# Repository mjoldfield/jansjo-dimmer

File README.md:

# Jansjö dimmer

This repository relates to a simple PWM dimmer designed ostensibly for
the Ikea Jansjö LED lamp.

See [the full article](http://mjoldfield.com/atelier/2017/11/jansjo-dimmer.html)
for more details.

## data

Experimental data from the prototypes:

### dutycycle-f

The variation of frequency with duty-cycle.

    $ gnuplot plotit.scr
    $ open out.pdf

### current-t

Various screen captures from the scope showing current against time.

## datasheets

Manufacturers' data for parts in the project.

## gerbers

PCB files as sent to the board manufacturer (Elecrow).

## kicad

PCB/schematic files

## panel

A Haskell program to generate a PDF to laser cut the front panel.

Given [stack](https://docs.haskellstack.org/en/stable/README/):

    $ stack build
    $ stack exec pdf-exe
    $ open *.pdf

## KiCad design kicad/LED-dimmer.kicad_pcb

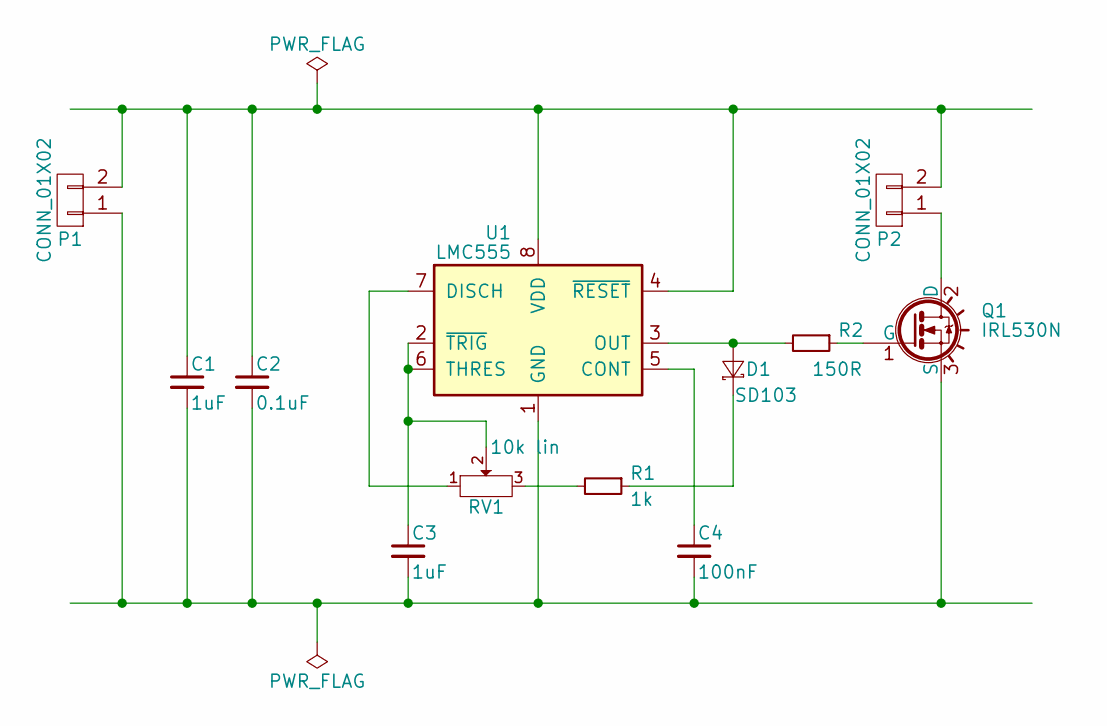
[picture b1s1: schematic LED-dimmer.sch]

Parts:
C1, C3: 1uF; C_0603
C2: 0.1uF; C_0603
C4: 100nF; C_0603
D1: SD103; D_SOD-123
P1, P2: CONN_01X02; Molex_MicroLatch-53253-0270_02x2.00mm_Straight
Q1: IRL530N; TO-263-2
R1: 1k; R_0603
R2: 150R; R_0603
RV1: 10k lin; Potentiometer_WirePads
U1: LMC555; SOIC-8_3.9x4.9mm_Pitch1.27mm

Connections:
unnamed: C1.1, C2.1, P1.2, P2.2, U1.4 (~RESET), U1.8 (VDD)
unnamed: C1.2, C2.2, C3.2, C4.2, P1.1, Q1.3 (S), U1.1 (GND)
unnamed: C3.1, RV1.2, U1.2 (~TRIG), U1.6 (THRES)
unnamed: C4.1, U1.5 (CONT)
unnamed: D1.1 (K), R1.1
unnamed: D1.2 (A), R2.2, U1.3 (OUT)
unnamed: P2.1, Q1.2 (D)
unnamed: Q1.1 (G), R2.1
unnamed: R1.2, RV1.3
unnamed: RV1.1, U1.7 (DISCH)

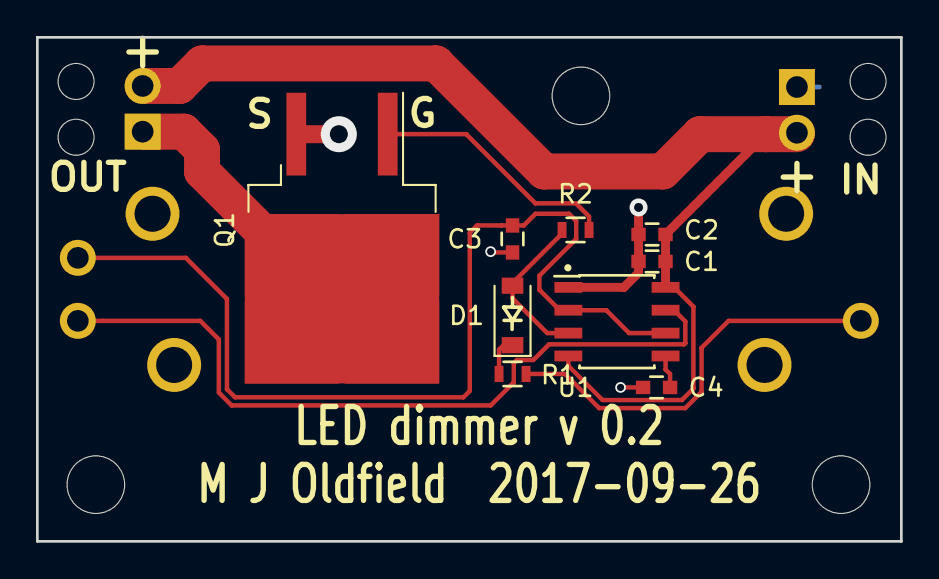
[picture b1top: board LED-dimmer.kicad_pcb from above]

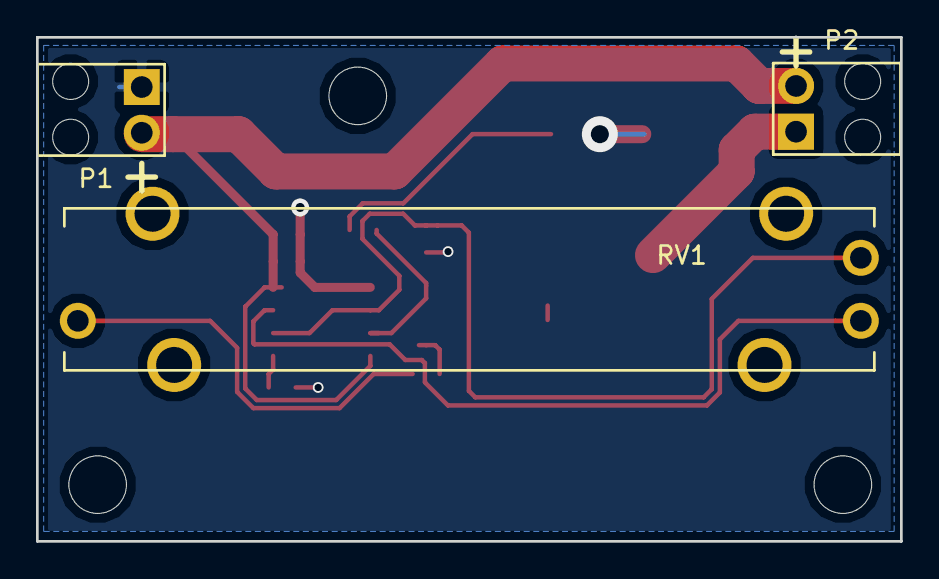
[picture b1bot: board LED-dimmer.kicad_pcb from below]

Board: 2 copper layers, 48.0 x 28.0 mm, 12 parts (3 on the bottom side), 10 nets.

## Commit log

2017-11-25 add files
2017-11-25 add link to article
